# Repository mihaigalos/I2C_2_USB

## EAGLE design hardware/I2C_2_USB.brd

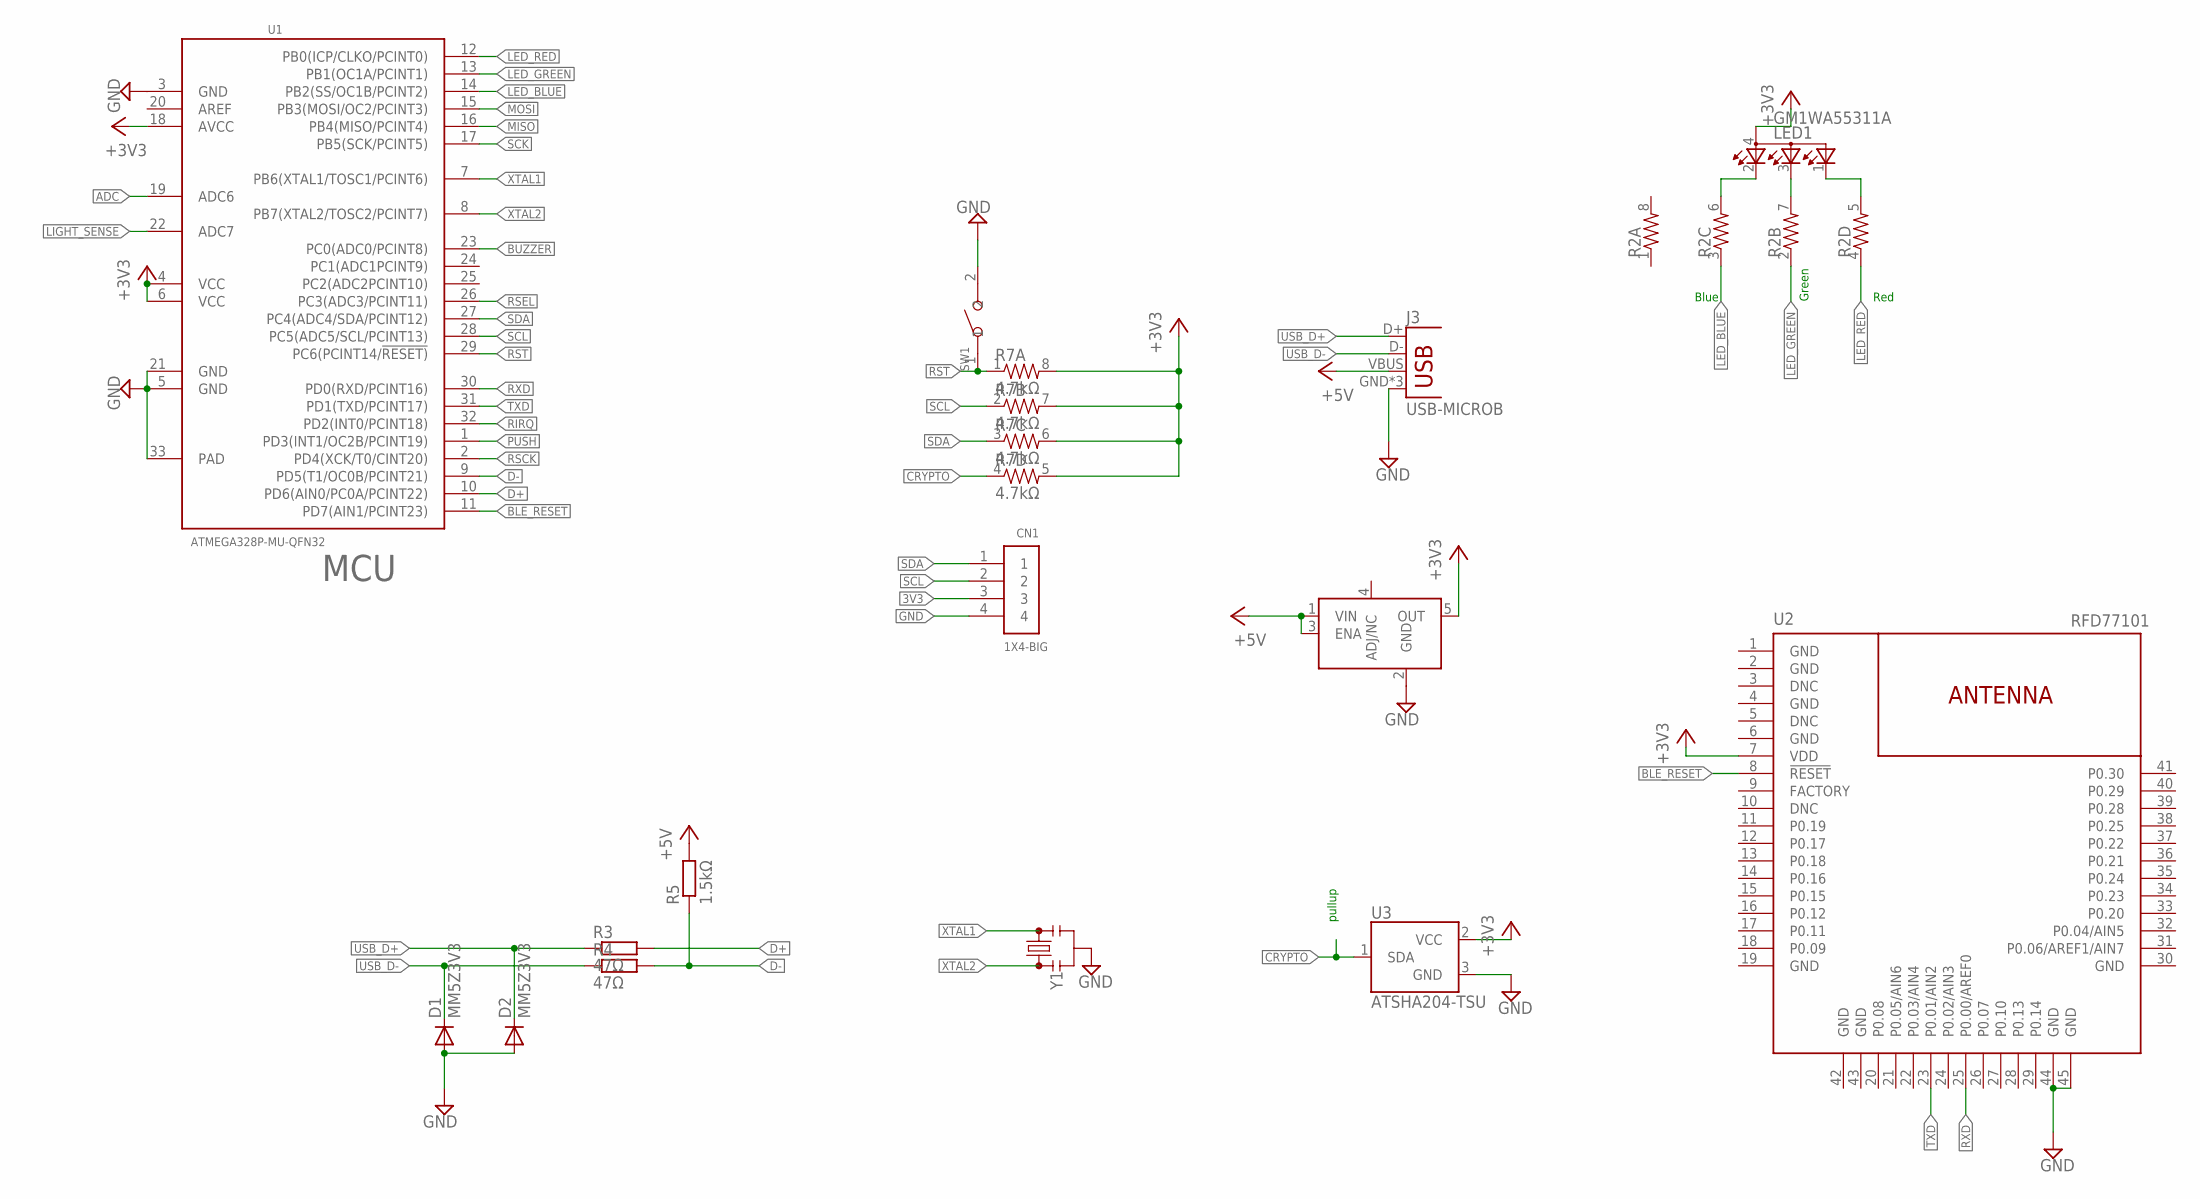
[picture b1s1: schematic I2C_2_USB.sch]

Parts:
CN1: 1X4-BIG; 1X04-BIG
D1, D2: MM5Z3V3; SOD523
J3: USB-MICROB
LED1: GM1WA55311A
R2: RESISTOR-ARRAY0603-ARV; 0603-ARV
R3, R4: 47Ω; R0603
R5: 1.5kΩ; R0603
R7: 4.7kΩ; 0603-ARV
SW1: SMD-BUTTON(2P-6.0X3.0X2.5MM)-DHT-1163S; SW2-4.0-6.0X3.0X2.5MM
U1: ATMEGA328P-MU-QFN32; QFN32G-0.5-5X5MM
U2: RFD77101
U3: ATSHA204-TSU; SOT23-3
U$4: LDCL015; SOT23-5
Y1: RESONATORSMD-3.2X1.3; RESONATOR-SMD-3.2X1.3

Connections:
3V3: CN1.3
+3V3: LED1.4 (A), R7.5 (2), R7.6 (2), R7.7 (2), R7.8 (2), U1.4 (VCC), U1.6 (VCC), U1.18 (AVCC), U2.7 (VDD), U3.2 (VCC), U$4.5 (OUT)
+5V: J3.VBUS, R5.2, U$4.1 (VIN), U$4.3 (ENA)
ADC: U1.19 (ADC6)
BLE_RESET: U1.11 (PD7(AIN1/PCINT23)), U2.8 (!RESET!)
BLUE: LED1.2 (CRED), R2.6 (2)
BUZZER: U1.23 (PC0(ADC0/PCINT8))
CRYPTO: R7.4 (1), U3.1 (SDA)
D+: R3.2, U1.10 (PD6(AIN0/PC0A/PCINT22))
D-: R4.2, R5.1, U1.9 (PD5(T1/OC0B/PCINT21))
GND: CN1.4, D1.A, D2.A, J3.GND, J3.MT1 (GND), J3.MT2 (GND), SW1.2, U1.3 (GND), U1.5 (GND), U1.21 (GND), U1.33 (PAD), U2.1 (GND), U2.2 (GND), U2.4 (GND), U2.6 (GND), U2.19 (GND), U2.30 (GND), U2.42 (GND), U2.43 (GND), U2.44 (GND), U2.45 (GND), U3.3 (GND), U$4.2 (GND), Y1.2
GREEN: LED1.3 (CBLUE), R2.7 (2)
LED_BLUE: R2.3 (1), U1.14 (PB2(SS/OC1B/PCINT2))
LED_GREEN: R2.2 (1), U1.13 (PB1(OC1A/PCINT1))
LED_RED: R2.4 (1), U1.12 (PB0(ICP/CLKO/PCINT0))
LIGHT_SENSE: U1.22 (ADC7)
MISO: U1.16 (PB4(MISO/PCINT4))
MOSI: U1.15 (PB3(MOSI/OC2/PCINT3))
PUSH: U1.1 (PD3(INT1/OC2B/PCINT19))
RED: LED1.1 (CGREEN), R2.5 (2)
RIRQ: U1.32 (PD2(INT0/PCINT18))
RSCK: U1.2 (PD4(XCK/T0/CINT20))
RSEL: U1.26 (PC3(ADC3/PCINT11))
RST: R7.1, SW1.1, U1.29 (PC6(PCINT14/!RESET))
RXD: U1.30 (PD0(RXD/PCINT16)), U2.25 (P0.00/AREF0)
SCK: U1.17 (PB5(SCK/PCINT5))
SCL: CN1.2, R7.2 (1), U1.28 (PC5(ADC5/SCL/PCINT13))
SDA: CN1.1, R7.3 (1), U1.27 (PC4(ADC4/SDA/PCINT12))
TXD: U1.31 (PD1(TXD/PCINT17)), U2.23 (P0.01/AIN2)
USB_D+: D2.C, J3.D+, R3.1
USB_D-: D1.C, J3.D-, R4.1
XTAL1: U1.7 (PB6(XTAL1/TOSC1/PCINT6)), Y1.3
XTAL2: U1.8 (PB7(XTAL2/TOSC2/PCINT7)), Y1.1

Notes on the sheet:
MCU
Blue
Green
Red
pullup

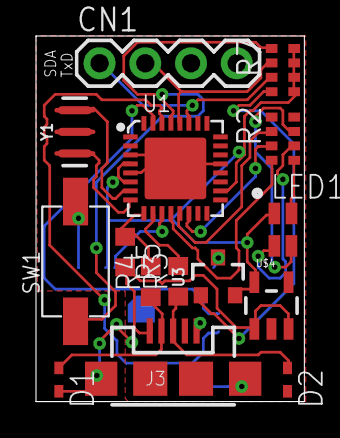
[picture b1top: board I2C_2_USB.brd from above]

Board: 2 copper layers, 14.9 x 20.3 mm, 16 parts (1 on the bottom side), 22 nets.

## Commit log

2017-12-13 Add RST pushbutton, GND planes
2017-12-13 Correct traces near pins
2017-12-13 Add QR & labels
2017-12-13 Rearrange I2C pins
2017-12-13 Move vias further away from R-array
2017-12-13 Trace improvement
2017-12-14 Connect SDA and TxD Lines
2017-12-14 Add crypto module & backside labels
2017-12-14 Add BLE module

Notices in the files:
parts and their libraries:
SparkFun: Licensing: CC v3.0 Share-Alike You are welcome to use this library for commercial purposes.
SparkFun-Retired: Licensing: Creative Commons ShareAlike 4.0 International - https://creativecommons.org/licenses/by-sa/4.0
SparkFun-RF: © 2015 RF Digital Corporation
